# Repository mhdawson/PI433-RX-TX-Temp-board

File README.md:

# Circuit board for Home alarm and temperature monitoring

This projects contains information and schematics for a board that
can be used with the Raspberry PI in order to provide the hardware for these
projects:

+ https://github.com/mhdawson/PI433WirelessRecvManager
+ https://github.com/mhdawson/PI433WirelessTXManager
+ https://github.com/mhdawson/PILocalTemp
+ https://github.com/mhdawson/HomeAlarm 
+ https://github.com/mhdawson/HouseDashboard

It combines the hardware needed for those projects onto a single
PCB with all the required components.

The project provides the kicad files (free from http://kicad.org) with the
board design that can be used to create the set of files needed
by a PCB manufacturer.

I validated the board by having batch built by www.pcbway.com, building one
and trying it out.  It seem to work but as always use at your own risk

It was my first board and I did not work to hard on it so there are a
few ways that it could be improved:

+ better silk screen layout - some of the screen identifying the parts is cut off

+ the solder holes for the antenas turned out to be under the RX module which
  is not what I had intended.

# Part List 

+ 1N4148 diode
+ 1K resistor
+ 4.7k resitor
+ BX-TM01-433 Transmitter module
+ RXB6 - receiver module
+ DS18B20 1-wire temperator sensor
+ 2 by 20pin header
+ 2 17cm wires for the antenas

See the references projects for more details 

# Key Files

+ 433-v1.kicad_pcb
+ 433-v1.net
+ 433-v1.pro
+ 433-v1.sch
+ 433-v1.dsn
+ 433-v1-cache.lib
+ 433-v1.xml

# Building gerber files needed to send to PCB manufacturer

+ check out the project
+ install kicad and open the v433-v1.pro project file
+ follow the instructions here: https://www.wayneandlayne.com/blog/2013/02/27/kicad-tutorial-gerber-file-generation/

# Pictures

## Kicad board layout

## Kicad wiring diagram 

## Front and back of board

## Front and back of populated board

## Board mounted in Pi

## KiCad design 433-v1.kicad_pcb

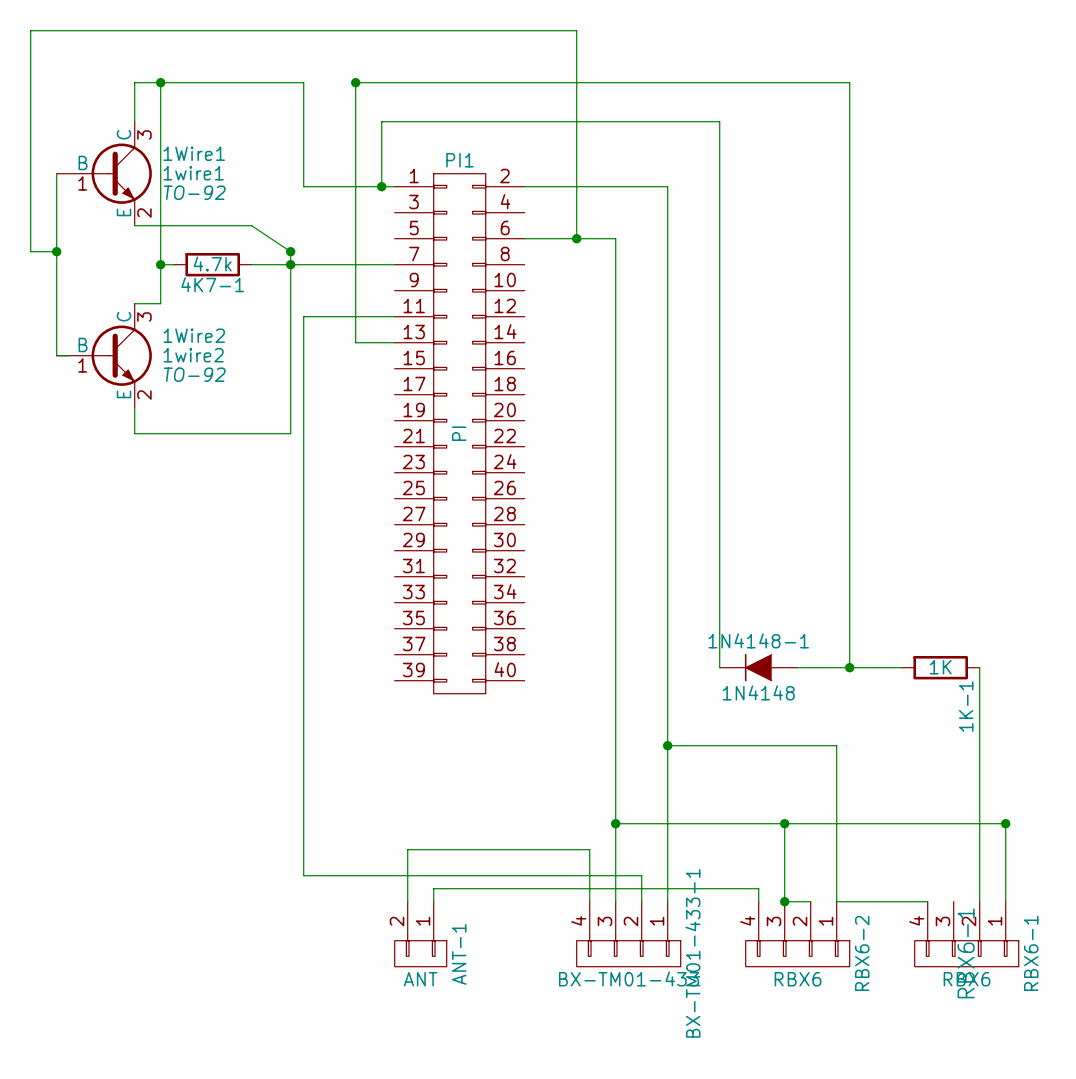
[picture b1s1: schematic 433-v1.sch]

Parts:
1K-1: 1K
1N4148-1: 1N4148
1Wire1: 1wire1; TO-92
1Wire2: 1wire2; TO-92
4K7-1: 4.7k
ANT-1: ANT
BX-TM01-433-1: BX-TM01-433
PI1: PI
RBX6-1: RBX6; RBX6-1
RBX6-2: RBX6

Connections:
unnamed: 1K-1.1, RBX6-1.2
unnamed: 1K-1.2, 1N4148-1.2 (A), PI1.13
unnamed: 1N4148-1.1 (K), 1Wire1.3 (C), 1Wire2.3 (C), 4K7-1.2, PI1.1
unnamed: 1Wire1.1 (B), 1Wire2.1 (B), BX-TM01-433-1.3, PI1.6, RBX6-1.1, RBX6-2.2, RBX6-2.3
unnamed: 1Wire1.2 (E), 1Wire2.2 (E), 4K7-1.1, PI1.7
unnamed: ANT-1.1, RBX6-2.4
unnamed: ANT-1.2, BX-TM01-433-1.4
unnamed: BX-TM01-433-1.1, PI1.2, RBX6-1.4, RBX6-2.1
unnamed: BX-TM01-433-1.2, PI1.11

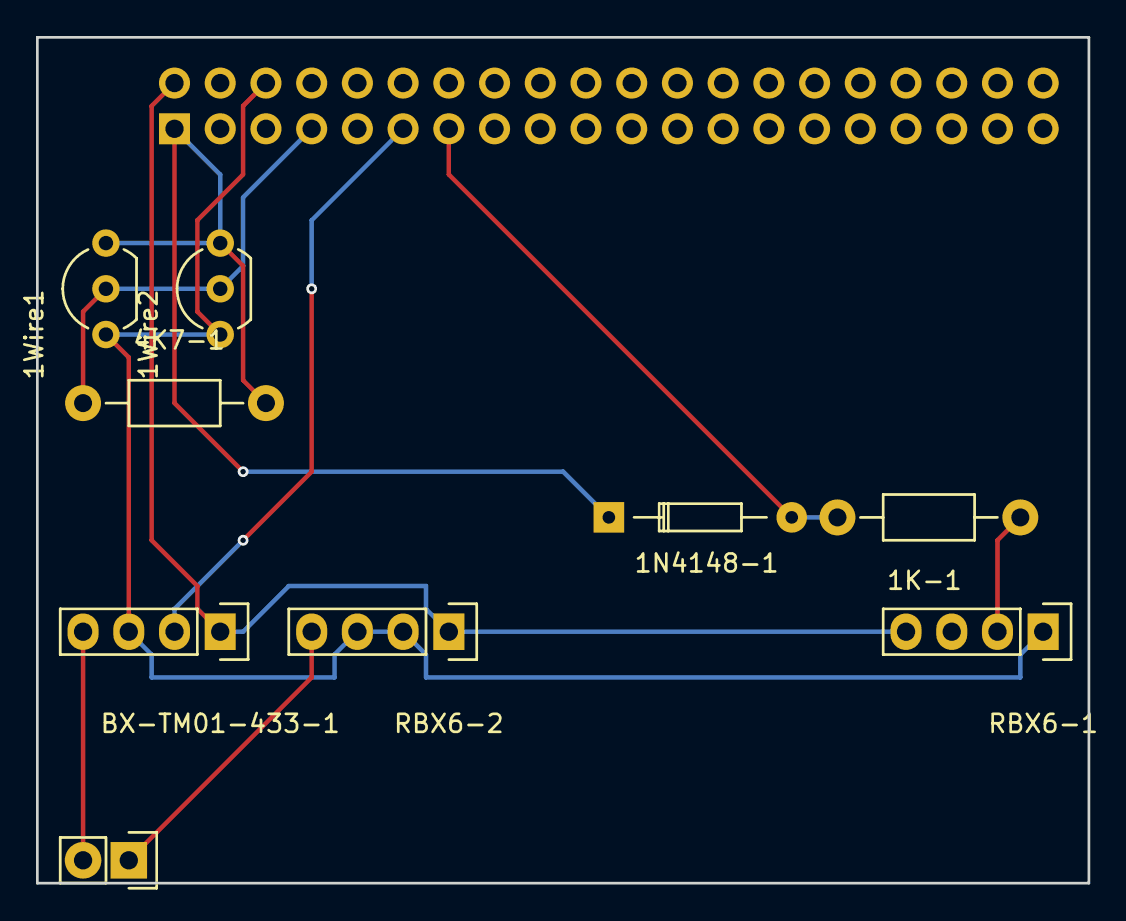
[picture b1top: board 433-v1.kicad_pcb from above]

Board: 2 copper layers, 58.4 x 47.0 mm, 10 parts (1 on the bottom side), 9 nets.

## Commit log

2015-11-06 Initial version of files
2015-11-06 Add titles for pictures in README.md
2015-11-06 Fix a few small issues in README.md
2015-11-06 Add info on creating gerber files
2015-11-06 Update link to includ http
2018-04-09 doc: fix typos
2021-11-10 Update README.md
    https://forum.kicad.info/t/warning-avoid-all-links-to-kicad-pcb-org-use-kicad-org/31521
